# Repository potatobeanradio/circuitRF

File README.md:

**EDA tool for RF design — for the RF community, by the RF community.**

circuitRF is a full-featured EDA tool for RF and microwave design — schematic capture + nonlinear analysis, layout and
EM and thermal simulation in one cross-platform application. **DC**, **S-parameter**, **harmonic-balance** and
**circuit envelope** analyses with first-class **loadpull / sourcepull**, over designs from a handful of components to
hierarchical, multi-port ones with thousands. A **layout editor** for PCB and MMIC work, with
substrate-aware microstrip components, schematic↔layout generation, **DRC** and **LVS**, and two-way
interchange with **Gerber + Excellon**, **GDSII**, **DXF** and `.kicad_pcb` boards. A **2.5D
electromagnetic solver** over the layout's own substrate stackup. **3D editor** for FEM / FDTD EM solutions (using Palace
/ EMerge / openEMS), and a built-in FEM **thermal solver**.  Supports command line and MCP.

**🎬 [circuitRF overview video](https://www.youtube.com/watch?v=s6teobulr_A)**<br>
&emsp;&emsp;<sub>🎬 [Simulation types](https://www.youtube.com/watch?v=Mn31hLSltSc)</sub><br>
&emsp;&emsp;<sub>🎬 [Schematic demo](https://www.youtube.com/watch?v=Nl2QQT9ML5c)</sub>

**📖 [Read the user documentation online](https://potatobeanradio.github.io/circuitRF/)**

circuitRF is for RF practitioners or researchers who can't justify the cost of traditional tools (or find those tools too heavy for a quick investigation): **power-amplifier, LNA, and mixer designers; RF EDA and device-modeling engineers; academic researchers; and capable hobbyists.** It was built largely **AI-assisted** (see
[AI-assisted development](#ai-assisted-development)).

## Features
- schematic + circuit simulation (DC, S-param, HB, Loadpull, Envelope)
- noise analysis (noise figure, noise circles, phase noise)
- 2D layout editor (imports and exports Gerber, GDSII, OASIS, DXF, .kicad_pcb)
- 3D geometry editor (imports / exports Step)
- hierarchy for all cell view types (including 3D)
- support for PDKs
- bondwire geometry editor and mutual inductance calculator
- Tuning and Optimization
- Monte Carlo, yield, corners, design centering and DOE
- 2.5D MoM
- 3D FEM and FDTD (using [Palace](https://github.com/awslabs/palace), [EMerge](https://github.com/FennisRobert/EMerge) and [openEMS](https://github.com/thliebig/openEMS))
- 3D FEM thermal solver
- command line and MCP server ([use it from an AI agent](#use-circuitrf-from-an-ai-agent))
- customizable plug-in architecture (add your own tools in Python or C#)
- Documentation with examples

[What circuitRF doesn't do yet](#what-circuitrf-doesnt-do-yet)

---

## Screenshots

### Schematic editor

<!-- IMAGE TO CREATE: docs/images/schematic-editor.png
     The schematic editor showing a single-FET power amplifier (Hero 2): an SDD FET with gate/drain bias
     (Vdc sources), input and output matching networks (R/L/C), a P1Tone RF source on the left, a Term on
     the output. Left: the Library Palette with component glyph tiles. Right/bottom: the Analyses panel
     with an HB power sweep set up. Show a couple of net labels and the green junction dots so the wiring
     reads clearly. -->
*Build hierarchical RF circuits on a virtualized canvas: drag from the palette, wire, label nets, set
parameters and sweeps, and Run.*

### Data Display — loadpull contours

<!-- IMAGE TO CREATE: docs/images/data-display-loadpull-contour.png
     The Data Display showing a loadpull result on a Smith chart: Pout (dBm) and PAE (%) contours over the
     load-Γ plane, with the MXP (max power) and MXE (max efficiency) markers called out, and a couple of
     interactive markers reading off impedance/value. A trace inspector card on the right shows the
     metric/colormap selection. Optionally a second rectangular plot (power sweep) docked alongside. -->
*Plot S-parameters, spectra, power sweeps, and loadpull contours; overlay measured Touchstone/`.spl`/
`.lpcwave` data on simulated results; plot EM results from MoM, FEM and FDTD solvers (including radiation 
patterns)*

### Layout editor

<!-- IMAGE PLACEHOLDER: docs/images/layout-editor.png — to be supplied by the repo owner. -->
*Draw and edit physical geometry on a technology-defined layer stack: microstrip components generated from
their schematic parameters, hierarchy with arrays, and export to GDSII, DXF and Gerber. MoM EM solver.*

### 3D editor

*Draw and edit in 3D and send to FEM or FDTD EM solvers or the built-in FEM thermal solver*

---

## Download

| Platform | Download |
|---|---|
| Windows, Intel/AMD | [circuitRF-1.8.4-win-x64-user.msi](https://github.com/potatobeanradio/circuitRF/releases/download/1.8.4/circuitRF-1.8.4-win-x64-user.msi) |
| Windows, ARM | [circuitRF-1.8.4-win-arm64-user.msi](https://github.com/potatobeanradio/circuitRF/releases/download/1.8.4/circuitRF-1.8.4-win-arm64-user.msi) |
| Windows, 32-bit | [circuitRF-1.8.4-win-x86-user.msi](https://github.com/potatobeanradio/circuitRF/releases/download/1.8.4/circuitRF-1.8.4-win-x86-user.msi) |
|  |  |
| macOS, Apple Silicon | [circuitRF-1.8.4-arm64.dmg](https://github.com/potatobeanradio/circuitRF/releases/download/1.8.4/circuitRF-1.8.4-arm64.dmg) |
| macOS, Intel | [circuitRF-1.8.4-x64.dmg](https://github.com/potatobeanradio/circuitRF/releases/download/1.8.4/circuitRF-1.8.4-x64.dmg) |
|  |  |
| Linux, Intel/AMD | [circuitRF-1.8.4-linux-x64.tar.gz](https://github.com/potatobeanradio/circuitRF/releases/download/1.8.4/circuitRF-1.8.4-linux-x64.tar.gz) |
| Linux, ARM | [circuitRF-1.8.4-linux-arm64.tar.gz](https://github.com/potatobeanradio/circuitRF/releases/download/1.8.4/circuitRF-1.8.4-linux-arm64.tar.gz) |
| Linux, Intel/AMD, AppImage | [circuitRF-1.8.4-linux-x64.AppImage](https://github.com/potatobeanradio/circuitRF/releases/download/1.8.4/circuitRF-1.8.4-linux-x64.AppImage) |
| Linux, ARM, AppImage | [circuitRF-1.8.4-linux-arm64.AppImage](https://github.com/potatobeanradio/circuitRF/releases/download/1.8.4/circuitRF-1.8.4-linux-arm64.AppImage) |

**Linux** — unpack and run `install.sh`. It writes only inside `~/.local`, puts `circuitrf` on your PATH
and registers the menu entry and file types; `--uninstall` removes it and leaves your work alone.

```sh
tar xzf circuitRF-1.8.4-linux-x64.tar.gz
./circuitRF-1.8.4/install.sh
```

**Linux AppImage**: download it, make it executable (`chmod +x circuitRF-1.8.4-linux-x64.AppImage`)
and run it. Nothing is installed, so keep it wherever you like. It does not update itself: when a new
version is out, its line in the Messages panel has a **Download** button that saves the new AppImage
next to the one you are running. AppImageUpdate can update it too. Use the tarball if you want updates
installed automatically.

**Installing for everyone on the machine?** The Windows `.msi` files without `-user`, and the `.deb`
files, are on the [releases page](https://github.com/potatobeanradio/circuitRF/releases). They need
administrator rights, so they cannot update themselves — they tell you when a new version is out
instead.

Automatic updates can be turned off in **Settings ▸ Security & Permissions**. Building the installers
yourself: [BUILDING.md](BUILDING.md).

---

## Use circuitRF from an AI agent

circuitRF is also an **MCP server**, so an AI agent can create workspaces, write designs, check
them, run simulations and read the results back. The installed application is the server; there is
nothing else to install.

**1. Pick a root folder.** The server can read and write only inside it. Use the folder your
designs live in, such as `~/designs`, not your whole home folder.

**2. Ask circuitRF for its configuration.** It prints the JSON an MCP client needs, with the
executable's full path filled in, and the matching Claude Code command:

| Platform | Command |
|---|---|
| macOS | `/Applications/circuitRF.app/Contents/MacOS/circuitRF serve --root ~/designs --print-config` |
| Windows | `circuitRF serve --root %USERPROFILE%\designs --print-config` (the installer puts circuitRF on `PATH`; **About circuitRF** shows the folder it is in) |
| Linux | `~/.local/bin/circuitrf serve --root ~/designs --print-config` |

**3. Register it with your client.** With Claude Code, run the `claude mcp add …` line it printed.
Most other clients take the printed JSON in their MCP settings. Start a new session afterwards,
because most clients load servers only when a session starts.

**4. Check that it answers.** Ask the agent to call circuitRF's `reference` tool. It should list
the reference topics.

Then read **[Designing with an AI agent](https://potatobeanradio.github.io/circuitRF/reference/ai-agents.html)**, which covers what
to tell the agent, which reference topics it should read first, and the design flow that works. The
full server description, including running it from a source build, is in
[The MCP Server](https://potatobeanradio.github.io/circuitRF/reference/mcp-server.html).

---

## Contributors are welcome — *especially RF domain experts*

circuitRF is meant to be **community-driven, by and for the RF engineering community.** We value **RF
domain knowledge as much as software experience.** If you design power amplifiers, LNAs, or mixers; build
RF EDA tooling; do device modeling; or develop transistor technology (GaN-on-SiC, GaN-on-Si, LDMOS, …),
**you are exactly who this project needs** — and circuitRF is a great place to use AI to build the
simulation features *you* want.

You do **not** need to be a professional software developer. If you've scripted in MATLAB or Python, you
have enough to start. Pair yourself with [Claude Code](https://www.anthropic.com/claude-code) (or your
AI assistant of choice) and let it do the heavy lifting on the C#.

---

## Architecture

circuitRF is built in strictly one-directional layers, and nothing below the UI knows the UI
exists. The layers, the engines, the enforced framework firewall and the source tree are described in
**[ARCHITECTURE.md](ARCHITECTURE.md)**.

---

## Developing circuitRF - Getting started

### 1. Install the tools

| Tool | Why | Get it |
|---|---|---|
| **.NET 10 SDK** | builds and runs circuitRF | <https://dotnet.microsoft.com/download/dotnet/10.0> |
| **Git** | clone the repos | <https://git-scm.com/downloads> |
| **Visual Studio Code** | edit + debug (lightweight, cross-platform) | <https://code.visualstudio.com/> |
| VS Code **C# Dev Kit** extension | C# editing/IntelliSense/debug in VS Code | <https://marketplace.visualstudio.com/items?itemName=ms-dotnettools.csdevkit> |

Verify the SDK is installed:
```bash
dotnet --version      # should print 10.x.x
```

### 2. Clone circuitRF

```bash
# cd to a working folder, then:
git clone https://github.com/potatobeanradio/circuitRF.git
```

### 3. Build and run

```bash
cd circuitRF

dotnet build      # restores packages + compiles everything
dotnet run --project src/Ui # from the circuitRF/ directory:
```

For faster simulations, run the Release build: `dotnet run --project src/Ui -c Release`.

### 4. Optional — testing & building the device workers

```bash
dotnet test       # optional 10-15 min of circuitRF development tests
```

A handful of loadpull tests read lab-measured `.spl`/`.lpcwave` files that are third-party data held
under terms that do not permit redistribution, so they have never been committed here. On a fresh
clone those tests report as **Skipped**, naming the path they wanted — they never fail, and a fresh
clone is green without them. Your own measurements in either format, dropped at those paths, exercise
the same code.

To build the device workers:
Needed only for PDKs whose device models ship as **compiled libraries**. `dotnet build` builds the
workers itself *if a C compiler is on PATH* — with none, it warns and carries on, and such a kit
refuses at Run.

Install one, then rebuild:

```powershell
winget install zig.zig                      # Windows  (or: scoop install zig)
```
```bash
brew install zig                            # macOS
sudo snap install zig --classic --beta      # Linux    (or your package manager)
```
```bash
dotnet build
```

macOS also runs those Linux models in a VM circuitRF ships — one extra ~330 MB download, once:

```bash
dotnet build src/Ui -p:CrfBuildVmImage=true
```

Alternatives to zig (MinGW `gcc`, Docker/Podman) and the rest:
[BUILDING.md ▸ Helper programs](BUILDING.md#helper-programs).

### Note: To package circuitRF as an app with installers

[**BUILDING.md**](BUILDING.md) has step-by-step instructions for producing the installers users
download: `.msi` (Windows x64/arm64/x86, per-machine and per-user), `.zip` (the Windows update
payload), `.dmg` (macOS arm64/x64), `.deb` (Linux x64/arm64) and `.tar.gz` (the Linux user-local
channel). One script per platform, run from the repository root.

---

## Running circuitRF

### To launch the GUI

```bash
# from the circuitRF/ directory:
dotnet run --project src/Ui
```

### To run circuitRF headless from the command line

Full CLI documentation: the
[Command Line chapter](https://potatobeanradio.github.io/circuitRF/reference/cli.html) of the user docs (design notes in
[`docs/design/cli.md`](docs/design/cli.md)).
An installed circuitRF is the command line too (`circuitrf <verb> …`, `circuitrf serve --root <dir>`
for MCP, set up as in [Use circuitRF from an AI agent](#use-circuitrf-from-an-ai-agent)) — for an
agent installing it unattended, see
[Installing for an agent](https://potatobeanradio.github.io/circuitRF/reference/mcp-server.html#install).

```bash
# S-parameters: sweep 1-3 GHz in 50 MHz steps, write a Touchstone file
dotnet run --project src/Cli -- sparam mycircuit.cnl --freq 1GHz:3GHz:50MHz -o mycircuit.s2p

# DC operating point
dotnet run --project src/Cli -- dc mycircuit.cnl

# Harmonic balance (runs the parametric sweep, if one wraps the analysis)
dotnet run --project src/Cli -- hb hero2.cnl --set Pavl_dbm=0 -o hero2.npy

# Loadpull over the directive's Gamma grid, exported as loadpull interchange
dotnet run --project src/Cli -- lp hero3.cnl --pin -20:1:15 -o hero3.spl

# Loadpull pursuit: search for the max-power and max-efficiency terminations
dotnet run --project src/Cli -- lpp hero3B.cnl --out-grid found.gam -o hero3B.npy

# Electromagnetic extraction of the layout a .cem names — no other arguments needed
dotnet run --project src/Cli -- em Amp.cem

# Author a correct initial document: a workspace, then a cell inside it
dotnet run --project src/Cli -- new workspace ~/designs/Amp --tech pcb-4layer_FR-4_62mil_1oz
dotnet run --project src/Cli -- new cell ~/designs/Amp Stage1 --views schematic,symbol

# Bring artwork or a component in: one interchange format to another, or a part as a cell
dotnet run --project src/Cli -- convert Filter.dxf -o gerbers/
dotnet run --project src/Cli -- import part parts/ --into ~/designs/Amp --cell SOT-23

# Is it well formed, does it resolve, is it sound? Runs no analysis and writes nothing
dotnet run --project src/Cli -- check ~/designs/Amp

# Does the artwork match the drawing? (LVS — read-only; -o writes a report)
dotnet run --project src/Cli -- lvs ~/designs/Amp/Stage1

# What did circuitRF DECIDE — which technology, which chain, what value?
dotnet run --project src/Cli -- explain Amp.cem
dotnet run --project src/Cli -- explain Stage1.csch --expr "Zopt*2"

# Read a result back, or a document, as one JSON document
dotnet run --project src/Cli -- read results/Amp_em.npy --only S --json

# Dump the elaborated netlist (flattened + parameters resolved) - great for debugging
dotnet run --project src/Cli -- elab mycircuit.cnl

# Print the MCP client configuration for this build (an MCP client starts the server itself;
# see "Use circuitRF from an AI agent" above, and point clients at a built dll, not at dotnet run)
dotnet run --project src/Cli -- serve --root ~/designs --print-config

# Help
dotnet run --project src/Cli
```

### Run a netlist through an engine (in code)

The whole pipeline is three calls — read → elaborate → run — which is exactly what the CLI does:

```csharp
using CircuitRF.Core.Netlist;
using CircuitRF.Core.Elaboration;
using CircuitRF.Engine;

var (lib, testbench) = CnlReader.ReadFile("mycircuit.cnl");
var netlist          = new Elaborator(lib).Elaborate(testbench);
var dataset          = SParameterEngine.Run(netlist, freqsHz);   // → a DataSet of DataCubes
```

---

## What circuitRF doesn't do yet

- **Transient analysis** — circuitRF is frequency-domain by design; there is no time-domain solver.

If you want to contribute to any of the above, please contact me.

---

## User documentation

The user documentation — Quick Start, New User's Guide and Reference Guide — is published at
**<https://potatobeanradio.github.io/circuitRF/>**. It lives in `docs/user/`, is what
**Help ▸ circuitRF Documentation** opens, and is served online straight from this repository,
so the web pages and the shipped pages are the same bytes. **It is generated, not hand-edited.** By
default a run rebuilds every page and leaves every figure as committed; recapturing figures from the
live application is opt-in, because it is nearly all of a full run's time:

```bash
dotnet run --project tools/DocGen -- --out docs/user                           # every page; figures as committed
dotnet run --project tools/DocGen -- --out docs/user --figures                 # ...and the figures of pages whose .md changed
dotnet run --project tools/DocGen -- --out docs/user --figure layout-editor    # ...and these figures, by name
dotnet run --project tools/DocGen -- --out docs/user --all-figures             # ...and every figure (minutes)
dotnet run --project tools/DocGen -- --page docs/user/src/reference/wbond.md   # just this page, in seconds
```

Prose is authored as Markdown under `docs/user/src/`; the pages under `docs/user/` are the output and
any edit to one is reverted by the next run. Figures are **vector captures of the running interface**
— the generator opens circuitRF headlessly, drives real views with real content, and writes SVG — so
they cannot drift from the application. Component parameter tables come from the live registry for
the same reason. There are no screenshots in this documentation and there are not meant to be.

`tools/DocGen/check-docs-current.sh` regenerates everything, figures included, and diffs, and fails if the committed output is not
what the generator produces. Run it after a UI change that moves a figure. The design note is
[`docs/design/user-docs-factory.md`](docs/design/user-docs-factory.md).

---

## Contributing

**Contributions are welcome and encouraged.** circuitRF is community-driven, by and for the RF community,
and **RF domain knowledge counts as much as software experience.** You don't need to be a career
programmer — MATLAB/Python scripting experience plus an AI assistant is plenty.

**Good first contributions:**
- Report Issues
- Use AI Agent to report issues, resolve them and initiate pull requests (PR)

**The ground rules:**
- The [architecture](ARCHITECTURE.md) is layered and the **UI firewall is enforced** — keep Avalonia out of
  `RfCore`/`Core`/`Engine`/`Design`/`Cli`/`Harmonica`/`WBond` (a CI test will catch you).
  Renderers stay Skia-only.
- **Every numerical change needs a `testdata/` regression test** within the tolerance the PRD states.
- The core is **MIT** — never ingest GPL code.
- Each subsystem has a `CLAUDE.md` with its local conventions; read the relevant one before diving in.

Substantial issues or new features should be discussed before a large PR, so we can point you at the right design
note (and save you rework).

---

## AI-assisted development

circuitRF was built largely with AI assistance (primarily [Claude](https://www.anthropic.com/claude) /
[Claude Code](https://www.anthropic.com/claude-code)), and **AI-assisted contributions are first-class
here.** The codebase is structured for it: spatial `CLAUDE.md` memory files capture the invariants and
local conventions of each subsystem, `docs/design/` holds the reasoning behind each part, and
`docs/skills/` holds step-by-step procedures you can hand directly to an AI agent.

This is the deliberate bet of the project: **an RF expert with an AI assistant can build the simulation
features they need.** If that describes you, you're in the right place.

---

## License

circuitRF's own source code is released under the **[MIT License](LICENSE)**. A future commercial
superset, if any, layers on through a clean extension boundary without forking the core.

The distribution also contains third-party components under their own terms, inventoried in
**[THIRD-PARTY-NOTICES.md](THIRD-PARTY-NOTICES.md)**. Three of them are copyleft and worth knowing about
before you redistribute a build:

- **[CSparse.NET](https://github.com/wo80/CSparse.NET)** (sparse complex LU, used throughout the engine)
  is **LGPL-2.1-only**. The packaged installers link it statically, so LGPL §6's relink requirement
  applies — satisfied here by publishing complete source, since anyone can substitute a modified
  CSparse.NET and rebuild. If you redistribute circuitRF binaries, that obligation travels with them.
- **[Open CASCADE Technology](https://github.com/Open-Cascade-SAS/OCCT)** (the geometry kernel behind
  booleans, fillets and STEP, run by `tools/geometry-worker`) is **LGPL-2.1-only with the Open CASCADE
  Exception**. The installers carry it unmodified as shared libraries in one replaceable folder, and
  its source is available under the written offer in the notices. The repository holds none of it:
  building from source fetches it with the recipe in `tools/geometry-worker/occt/`.
- **[`tools/osdi-worker/osdi.h`](tools/osdi-worker/osdi.h)** is **MPL-2.0** (© 2022 SemiMod GmbH, from
  ngspice). MPL is copyleft at file scope: the file may live inside an MIT project, but it stays MPL
  and its header notice must not be removed.

No strong-copyleft (GPL/AGPL) code is ingested, and none is planned — see `CLAUDE.md` for the standing
rule on learning from GPL simulators without copying them.

---

## Acknowledgments

- **[Avalonia](https://avaloniaui.net/)** (cross-platform UI — MIT)
- **[SkiaSharp](https://github.com/mono/SkiaSharp)** (2D rendering — MIT)
- **[CSparse.NET](https://github.com/wo80/CSparse.NET)** (sparse complex LU — **LGPL-2.1-only**)
- **[Open CASCADE Technology](https://github.com/Open-Cascade-SAS/OCCT)** (geometry kernel — **LGPL-2.1-only** with the Open CASCADE Exception 1.0); circuitRF uses facilities provided by Open CASCADE Technology
- **[NumFlat](https://github.com/sinshu/numflat)** (dense linear algebra — MIT)
- **[FftFlat](https://github.com/sinshu/FftFlat)** (FFT — MIT)
- **[Clipper2](https://github.com/AngusJohnson/Clipper2)** (integer-coordinate polygon clipping and offsetting, used by the layout editor — Boost Software License)
- **[gdstk](https://github.com/heitzmann/gdstk)** (OASIS and GDSII reading and writing for the (gdstk) import and export commands, run by `tools/gdstk-worker` — Boost Software License), with its bundled Clipper 6.4.2 (Boost Software License), **[Qhull](http://www.qhull.org)** (Qhull licence) and **[zlib](https://zlib.net)** (zlib licence), all linked statically into the one worker program
- **[CommunityToolkit.MVVM](https://github.com/CommunityToolkit/dotnet)** (MIT)
- **[Dock.Avalonia](https://github.com/wieslawsoltes/Dock)** (docking — MIT)
- **[Material.Icons.Avalonia](https://github.com/SKProCH/Material.Icons)** (icon set — MIT)
- **[PureHDF](https://github.com/Apollo3zehn/PureHDF)** (HDF5 export — MIT)
- **[Markdig](https://github.com/xoofx/markdig)** (Markdown rendering — BSD-2-Clause)
- **[Svg](https://github.com/svg-net/SVG)** (MS-PL) and **[Svg.Skia](https://github.com/wieslawsoltes/Svg.Skia)** (MIT), used by `tools/IconGen` at packaging time
- Fonts: **IBM Plex Sans** and **Inter** (SIL Open Font License 1.1), **DejaVu Sans** (Bitstream Vera Fonts License)
- **[`osdi.h`](tools/osdi-worker/osdi.h)** from the ngspice OSDI component (© 2022 SemiMod GmbH — MPL-2.0)

Full terms, and what each one obliges you to do if you redistribute a build, are in
**[THIRD-PARTY-NOTICES.md](THIRD-PARTY-NOTICES.md)**.

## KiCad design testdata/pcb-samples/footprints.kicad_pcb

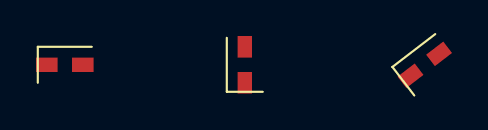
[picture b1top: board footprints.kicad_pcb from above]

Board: 2 copper layers, 4 parts (1 on the bottom side), 2 nets, no tracks yet.

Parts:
R10, R20, R30, R40: PAIR_2mm

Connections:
A: R10.1, R20.1, R30.1, R40.1
B: R10.2, R20.2, R30.2, R40.2

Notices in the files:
README.md:
License: MIT
